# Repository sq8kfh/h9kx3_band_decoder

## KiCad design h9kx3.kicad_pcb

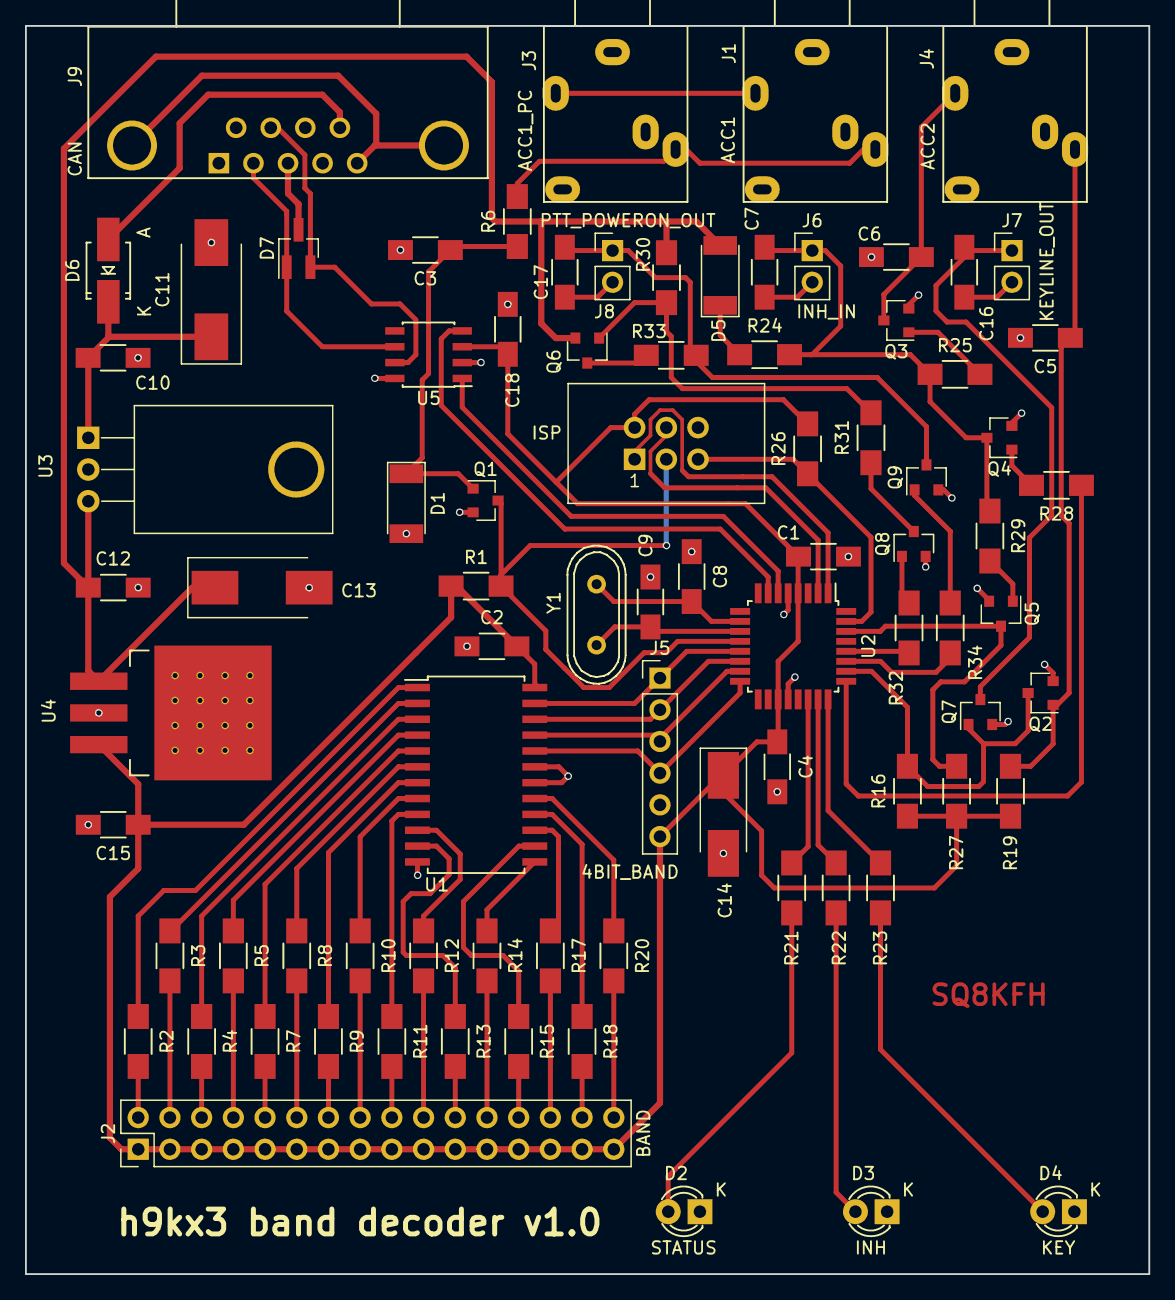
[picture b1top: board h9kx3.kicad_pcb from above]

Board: 2 copper layers, 90.0 x 100.0 mm, 84 parts (0 on the bottom side), 80 nets.

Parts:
C1, C2, C4, C10, C12, C15, C18: 100n; C_1206_HandSoldering
C3, C5, C6, C7, C16, C17: 1n; C_1206_HandSoldering
C8, C9: 22p; C_1206_HandSoldering
C11, C13: 100u; CP_Tantalum_Case-D_EIA-7343-31_Hand
C14: 100u; CP_Tantalum_Case-C_EIA-6032-28_Hand
D1, D5: 1N4148; D_MELF_Standard
D2: STATUS; LED-3MM
D3: INH; LED-3MM
D4: KEY; LED-3MM
D6: S1A; SMA_Handsoldering
D7: NUP2105; SOT-23_Handsoldering
ISP: AVR-ISP-6; IDC_Header_Straight_6pins
J1: ACC1; LUMBERG_1503_XX
J2: BAND; Pin_Header_Straight_2x16_Pitch2.54mm
J3: ACC1_PC; LUMBERG_1503_XX
J4: ACC2; LUMBERG_1503_XX
J5: 4BIT_BAND; Pin_Header_Straight_1x06_Pitch2.54mm
J6: INH_IN; Pin_Header_Straight_1x02_Pitch2.54mm
J7: KEYLINE_OUT; Pin_Header_Straight_1x02_Pitch2.54mm
J8: PTT_POWERON_OUT; Pin_Header_Straight_1x02_Pitch2.54mm
J9: CAN; DB9FC-DHP8-7.2mm
Q1, Q2, Q8, Q9: BC817-40; SOT-23
Q3, Q4, Q5, Q7: BC817; SOT-23
Q6: MMBT3906; SOT-23
R1, R16, R19, R24, R26, R27, R30, R32, R33, R34: 10k; R_1206_HandSoldering
R2, R3, R4, R5, R7, R8, R9, R10, R11, R12, R13, R14, R15, R17, R18, R20: 270R; R_1206_HandSoldering
R6, R21, R22, R23, R31: 220R; R_1206_HandSoldering
R25, R28, R29: 220; R_1206_HandSoldering
U1: 74LS154; SOIC-24W_7.5x15.4mm_Pitch1.27mm
U2: ATMEGA32M1-AU; TQFP-32_7x7mm_Pitch0.8mm
U3: LM7810CT; TO-220_Horizontal
U4: LM7805CT; TO-263-3Lead
U5: MCP2551-I/SN; SOIC-8_3.9x4.9mm_Pitch1.27mm
Y1: Crystal; Crystal_HC49-U_Vertical

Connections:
+5V: C1.2, C2.2, C4.1, C14.1, C15.1, C18.2, ISP.2, J2.1, J2.3, J2.5, J2.7, J2.9, J2.11, J2.13, J2.15, J2.17, J2.19, J2.21, J2.23, J2.25, J2.27, J2.29, J2.31, J5.6, R1.1, R16.1, R19.1, R26.2, R27.1, U1.24, U2.4, U2.19, U4.3, U5.3
/BAND_0: J5.1, U1.23, U2.13
/BAND_1: J5.2, U1.22, U2.14
/BAND_2: J5.3, U1.21, U2.15
/BAND_3: J5.4, U1.20, U2.16
/CAN_RX: U2.7, U5.4
/CAN_TX: U2.6, U5.1
/INHIBITS: R28.1, U2.25
/INHIBITS_IN: Q5.3, R27.2, U2.30
/KEYLINE: Q2.3, Q7.1, R16.2, U2.26
/KX3_POWER_ON: R32.1, U2.28
/LED_INH: R22.1, U2.23
/LED_KEY: R23.1, U2.24
/LED_STATUS: R21.1, U2.22
/MISO: ISP.1, U2.1
/MOSI: ISP.4, U2.2
/PTT_OUT: R34.1, U2.27
/RESET: ISP.5, R26.1, U2.31
/RX_SCK: ISP.3, Q1.3, R1.2, U2.12
GND: C1.1, C2.1, C3.2, C4.2, C5.2, C6.2, C7.2, C8.1, C9.1, C10.2, C11.2, C12.2, C13.2, C14.2, C15.2, C16.2, C17.2, C18.1, D1.2, D2.1, D3.1, D4.1, D7.3, ISP.6, J1.1, J3.1, J4.1, J5.5, J6.2, J7.2, J8.2, J9.3, J9.6, Q1.2, Q2.2, Q3.2, Q4.2, Q5.2, Q7.2, Q8.2, Q9.2, U1.12, U1.18, U1.19, U2.5, U2.20, U3.2, U3.None, U4.2, U5.2, U5.8
unnamed: C3.1, D1.1, Q1.1, R6.1
unnamed: C5.1, J4.3, Q2.1, R19.2
unnamed: C6.1, J4.2, Q3.3
unnamed: C7.1, J6.1, Q4.3, R24.2, R25.1, R29.1
unnamed: C8.2, U2.10, Y1.1
unnamed: C9.2, U2.11, Y1.2
unnamed: C10.1, C11.1, D6.1, U3.1
unnamed: C16.1, J7.1, Q7.3
unnamed: C17.1, J8.1, Q9.3, R33.1
unnamed: D2.2, R21.2
unnamed: D3.2, R22.2
unnamed: D4.2, R23.2
unnamed: D5.1, R24.1
unnamed: D6.2, J9.9
unnamed: D7.1, J9.2, U5.6
unnamed: D7.2, J9.7, U5.7
unnamed: J1.2, J3.2
unnamed: J1.3, J3.3, R6.2
unnamed: J2.2, R2.2
unnamed: J2.4, R3.2
unnamed: J2.6, R4.2
unnamed: J2.8, R5.2
unnamed: J2.10, R7.2
unnamed: J2.12, R8.2
unnamed: J2.14, R9.2
unnamed: J2.16, R10.2
unnamed: J2.18, R11.2
unnamed: J2.20, R12.2
unnamed: J2.22, R13.2
unnamed: J2.24, R14.2
unnamed: J2.26, R15.2
unnamed: J2.28, R17.2
unnamed: J2.30, R18.2
unnamed: J2.32, R20.2
unnamed: J9.0, J9.5
unnamed: Q3.1, R25.2
unnamed: Q4.1, R28.2
unnamed: Q5.1, R29.2
unnamed: Q6.1, R30.1, R31.2
unnamed: Q6.3, R33.2
unnamed: Q8.1, R32.2
unnamed: Q8.3, R31.1
unnamed: Q9.1, R34.2
unnamed: R2.1, U1.1
unnamed: R3.1, U1.2
unnamed: R4.1, U1.3
unnamed: R5.1, U1.4
unnamed: R7.1, U1.5
unnamed: R8.1, U1.6
unnamed: R9.1, U1.7
unnamed: R10.1, U1.8
unnamed: R11.1, U1.9
unnamed: R12.1, U1.10
unnamed: R13.1, U1.11
unnamed: R14.1, U1.13
unnamed: R15.1, U1.14
unnamed: R17.1, U1.15
unnamed: R18.1, U1.16
unnamed: R20.1, U1.17
VDD: C12.1, C13.1, D5.2, Q6.2, R30.2, U3.3, U4.1

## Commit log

2019-05-07 init
2019-05-08 pcb init
2019-05-09 v1.0rc
2019-05-09 name fix
2019-05-24 Q1-Q9 SOT-23 -> SOT-23_Handsoldering
2019-05-25 elements value
2019-05-25 D1,D5 MELF->MiniMELF
2019-05-29 fixed a elements values
